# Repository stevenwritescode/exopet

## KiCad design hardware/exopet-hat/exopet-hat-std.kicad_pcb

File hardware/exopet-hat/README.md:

# ExoPet HAT — KiCad Project

Rev 1 hardware per `docs/superpowers/specs/2026-07-27-exopet-hat-design.md`.

- `exopet-hat.kicad_pro` — project
- `exopet-hat.kicad_sch` — schematic (stage 1: capture complete, layout not started)

## Status

- [x] Schematic capture (all blocks from the spec)
- [x] Review pass — done via datasheet verification (see below); GUI
      eyeball still welcome
- [x] Footprint assignment + LCSC part numbers (`exopet-hat-bom.csv`,
      see `BOM-NOTES.md` for confidence levels)
- [x] Board layout — generated placement + freerouting autoroute
      (`tools/gen_board.py`, `tools/flip_backs.py`, `tools/finish_board.py`
      pipeline); DRC fully clean (0 violations)
- [ ] Human eyeball pass on the routed board in the KiCad GUI
- [ ] JLCPCB DFM check + fab package (gerbers/BOM/CPL)
- [ ] Order prototypes

## Layout notes (rev 1)

- **Terminal grouping (per Steven):** front edge = the four relay
  channels as separated blocks, CH1 CH2 CH3 then the CH4 dry contact
  last; left edge = sensor stack: FLOAT1, FLOAT2, TEMP (3-pos screw
  terminal — 3V3/DATA/GND, no plugs or soldering).
- **Float switch inputs added** (they were missing!): FLOAT1 → GPIO16
  (tank, matches existing hub code), FLOAT2 → GPIO12 (sump spec). Each
  has 10k pull-up, 1k series protection, 100nF filter on board.
- All terminals are Phoenix PT-1,5 3.5 mm pitch (17.5 A rated — loads
  are ≤1 A).
- All SMD is on the **back side**, nested in pin-free channels between
  the through-hole fields; top side is through-hole only.
- **J5 (JST temp connector) and the TRS jack were cut** — temperature is
  the 3-pos screw terminal.
- **J2 (aux 12V input) was cut** — barrel jack is the sole input.
- Signal tracks are 0.25 mm (autorouted); bulk current rides the
  full-board GND pours and short paths. Rev 2: netclass-driven widths.
- GND zones both sides, thermal-relief pads, min spoke count relaxed to
  1 (relieved pads also carry routed GND tracks).

## Datasheet verification (done in lieu of skipped human review)

- **EZO-pH socket (J7/J12)** — verified against Atlas EZO-pH datasheet
  v6.1: top row GND, TX/SDA, RX/SCL; bottom row VCC, PRB, PGND.
- **G5LE-1 relay** — verified against Omron K100-E1-08 datasheet: coil on
  terminals 2/5, COM 1, NO 3, NC 4; KiCad footprint pad geometry matches
  the datasheet mounting-hole pattern.
- **Pololu D24V50F5** — confirmed 5 pins (EN, VIN, 2×GND, VOUT); socket is
  now 1×5. **Physical pin order must be confirmed against the module
  silkscreen at layout time.**

## pH: deferred to rev 2

Rev 1 has **no pH input** (decision 2026-07-27). The Atlas datasheet
requires electrical isolation near pumps/valves for commercial use, so
rev 2 will add the EZO socket + BNC behind an ADM3260 isolation stage
(reference circuit: EZO-pH datasheet p.8). GPIO2/3 (header pins 3/5)
are left unconnected and reserved for it.

## Conventions

- Connectivity uses global labels (`+12V`, `GPIO17`, `1WIRE_DATA`, …)
  rather than long wires — check the label, not the line.
- U2 uses the ULN2003 symbol; the BOM part is **TBD62003APG**
  (pin-compatible DMOS array, 3.3 V-safe inputs).
- PSU1 is the socketed Pololu D24V50F5 5 V/5 A buck module (rev 2:
  integrate a TPS54531 circuit).
- **Verify before layout:** PSU1 socket pin order against the
  D24V50F5 module silkscreen (EN, VIN, 2×GND, VOUT).

## Opening

KiCad 8+. `File → Open Project → exopet-hat.kicad_pro`.
Run ERC: Inspect → Electrical Rules Checker.

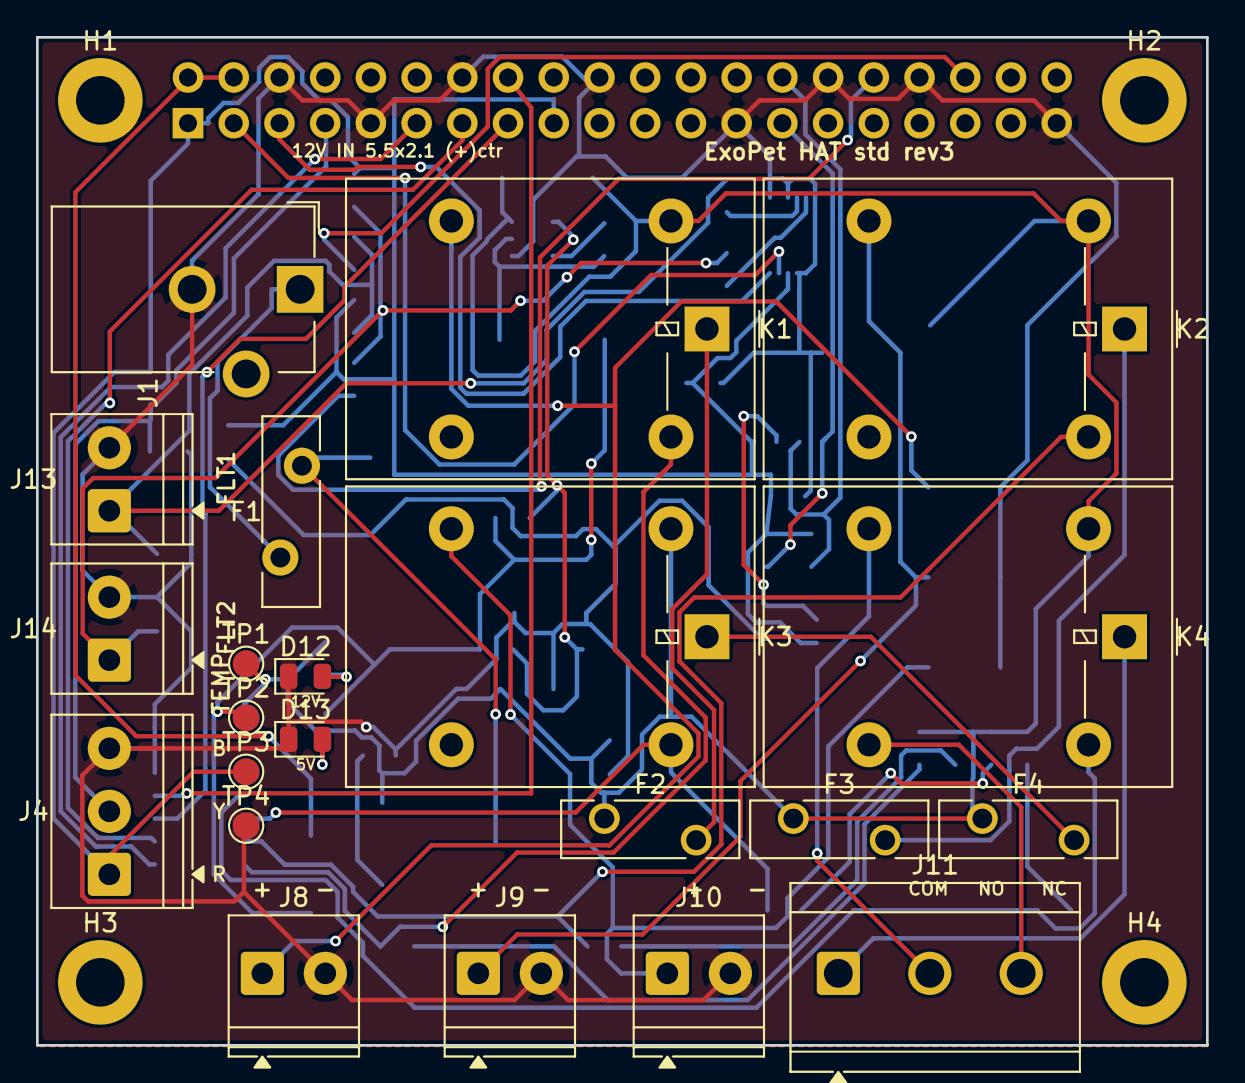
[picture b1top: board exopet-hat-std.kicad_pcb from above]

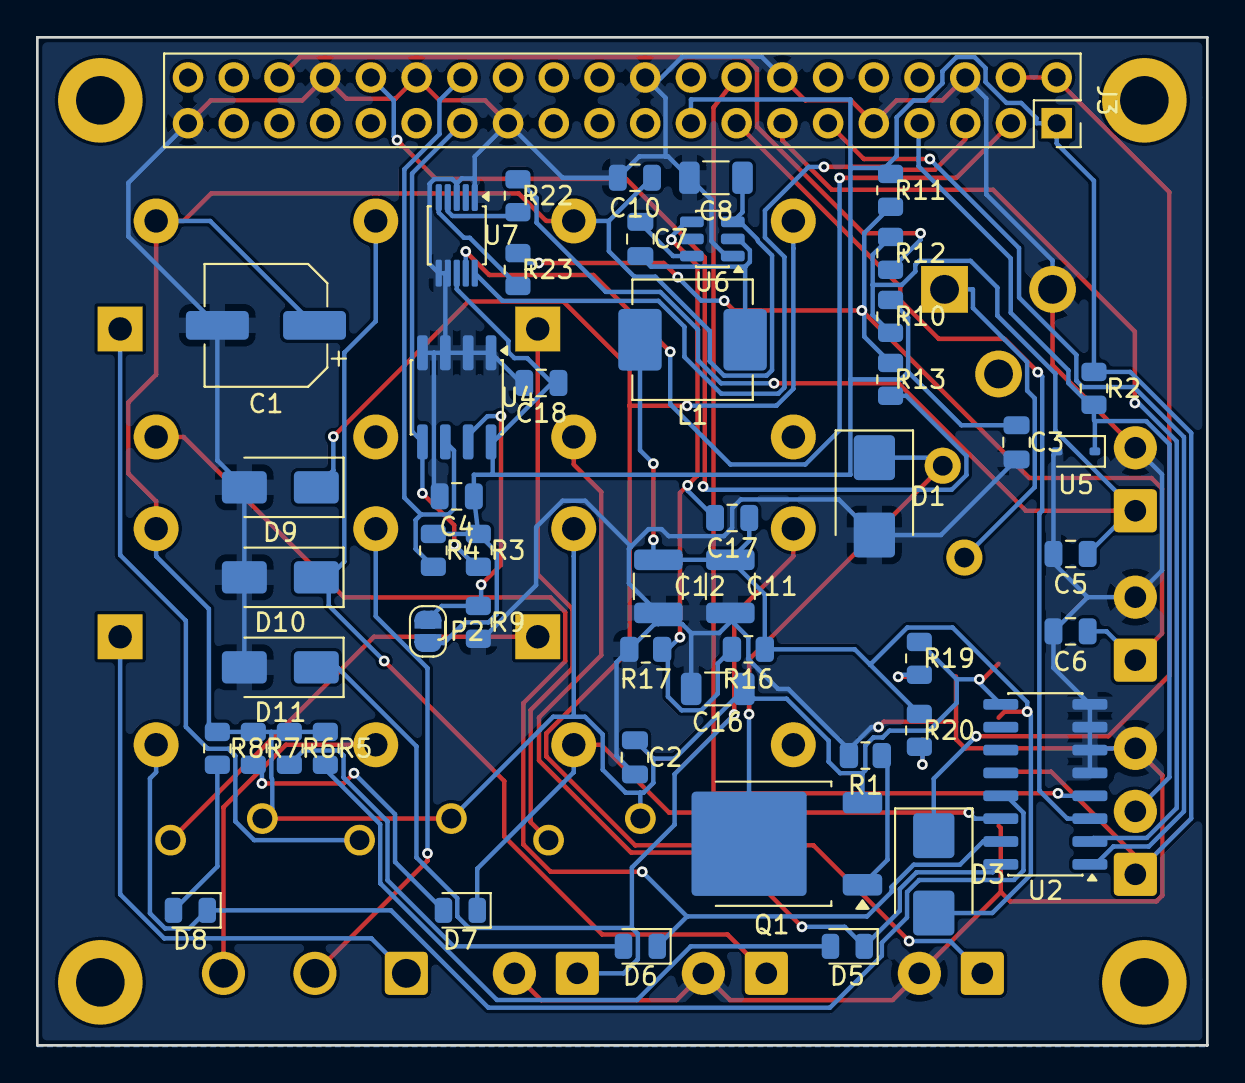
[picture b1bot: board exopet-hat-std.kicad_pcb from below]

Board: 2 copper layers, 65.0 x 56.0 mm, 77 parts (51 on the bottom side), 46 nets.

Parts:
C1: CP_Elec_6.3x7.7
C2, C3, C4, C5, C6, C7, C10, C17, C18: C_0805_2012Metric
C8, C16: C_1206_3216Metric
C11, C12: C_1210_3225Metric
D1, D3: D_SMB
D5, D6, D7, D8, D12, D13: LED_0805_2012Metric
D9, D10, D11: D_SMA
F1: Fuse_Bourns_MF-RG500
F2, F3, F4: Fuse_Bourns_MF-RHT100
H1, H2, H3, H4: MountingHole_2.7mm_M2.5_DIN965_Pad
J1: BarrelJack_CUI_PJ-102AH_Horizontal
J3: PinSocket_2x20_P2.54mm_Vertical
J4: TerminalBlock_Phoenix_PT-1,5-3-3.5-H_1x03_P3.50mm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; TerminalBlock_Phoenix_PT-1,5-3-3.5-H_1x03_P3.50mm_Horizontal
J8, J9, J10, J13, J14: TerminalBlock_Phoenix_PT-1,5-2-3.5-H_1x02_P3.50mm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; TerminalBlock_Phoenix_PT-1,5-2-3.5-H_1x02_P3.50mm_Horizontal
J11: TerminalBlock_CUI_TB007-508-03_1x03_P5.08mm_Horiz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; TerminalBlock_CUI_TB007-508-03_1x03_P5.08mm_Horizontal
JP2: SolderJumper-2_P1.3mm_Open_RoundedPad1.0x1.5mm
K1, K2, K3, K4: Relay_SPDT_Omron-G5LE-1
L1: L_Vishay_IHLP-2525
Q1: TO-252-2
R1, R2, R3, R4, R5, R6, R7, R8, R9, R10, R11, R12, R13, R16, R17, R19, R20, R22, R23: R_0805_2012Metric
TP1, TP2, TP3, TP4: TestPoint_Pad_D1.5mm
U2: SOIC-16_3.9x9.9mm_P1.27mm
U4: SOIC-8_3.9x4.9mm_P1.27mm
U5: D_SOD-323
U6: SOT-23-6
U7: MSOP-10_3x3mm_P0.5mm

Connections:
1WIRE_DATA: J3.7, J4.2, R2.2, U5.1
+3V3: C3.1, C4.1, C18.1, J3.1, J3.17, J4.1, JP2.2, R2.1, R3.1, R4.1, R10.1, R11.1, TP3.1, U4.8, U7.8
+5V: D3.1, J3.2, J3.4
+5V_BUCK: C11.1, C12.1, C17.1, D3.2, L1.2, R16.1, R20.1, TP2.1
+12V: C1.1, C2.1, C8.1, C10.1, C16.1, F2.1, F3.1, F4.1, K1.2, K2.2, K3.2, K4.2, Q1.3, R5.1, R6.1, R7.1, R8.1, R19.1, TP1.1, U2.9, U6.3
+12V_F: D1.1, F1.2, Q1.2
+12V_IN: F1.1, J1.1
BUCK_BOOT: C7.1, U6.6
BUCK_FB: C17.2, R16.2, R17.1, U6.4
BUCK_SW: C7.2, L1.1, U6.2
CH1_FUSED: F2.2, K1.1
CH1_OUT: D9.1, J8.1, K1.3
CH2_FUSED: F3.2, K2.1
CH2_OUT: D10.1, J9.1, K2.3
CH3_FUSED: F4.2, K3.1
CH3_OUT: D11.1, J10.1, K3.3
CH4_COM: J11.1, K4.1
CH4_NC: J11.3, K4.4
CH4_NO: J11.2, K4.3
EEPROM_SCL: J3.28, R4.2, U4.6
EEPROM_SDA: J3.27, R3.2, U4.5
EEPROM_WP: JP2.1, R9.1, U4.7
FLOAT1_GPIO: J3.36, R12.2
FLOAT1_SW: C5.1, J13.1, R10.2, R12.1, R22.1
FLOAT2_GPIO: J3.32, R13.2
FLOAT2_SW: C6.1, J14.1, R11.2, R13.1, R23.1
FLT1_SENSE: R22.2, U7.4
FLT2_SENSE: R23.2, U7.5
GND: C1.2, C2.2, C3.2, C4.2, C5.2, C6.2, C8.2, C10.2, C11.2, C12.2, C16.2, C18.2, D1.2, D9.2, D10.2, D11.2, D12.1, D13.1, J1.2, J3.6, J3.9, J3.14, J3.20, J3.25, J3.30, J3.34, J3.39, J4.3, J8.2, J9.2, J10.2, J13.2, J14.2, R1.2, R9.2, R17.2, TP4.1, U2.5, U2.6, U2.7, U2.8, U4.1, U4.2, U4.3, U4.4, U5.2, U6.1, U7.1, U7.3, U7.6, U7.7
GPIO17: J3.11, U2.1
GPIO22: J3.15, U2.3
GPIO23: J3.16, U2.4
GPIO27: J3.13, U2.2
I2C1_SCL: J3.5, U7.10
I2C1_SDA: J3.3, U7.9
LED1_A: D5.2, R5.2
LED2_A: D6.2, R6.2
LED3_A: D7.2, R7.2
LED4_A: D8.2, R8.2
LED5V_A: D13.2, R20.2
LED12V_A: D12.2, R19.2
Q1_G: Q1.1, R1.1
RLY1_DRV: D5.1, K1.5, U2.16
RLY2_DRV: D6.1, K2.5, U2.15
RLY3_DRV: D7.1, K3.5, U2.14
RLY4_DRV: D8.1, K4.5, U2.13

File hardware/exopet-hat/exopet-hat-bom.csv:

"Reference","Value","Footprint","LCSC"
"C1","330uF 25V low-profile <=7.7mm","Capacitor_SMD:CP_Elec_6.3x7.7","VERIFY"
"C2-C6","100nF","Capacitor_SMD:C_0805_2012Metric","C49678"
"D1","SMBJ16A","Diode_SMD:D_SMB","VERIFY"
"D5-D8","green","LED_SMD:LED_0805_2012Metric","C2297"
"D9-D11","SS34","Diode_SMD:D_SMA","C8678"
"F1","MF-RG500 5A","Fuse:Fuse_Bourns_MF-RG500","VERIFY"
"F2-F4","MF-RHT100 1A","Fuse:Fuse_Bourns_MF-RHT100","VERIFY"
"J1","12V DC in","Connector_BarrelJack:BarrelJack_CUI_PJ-102AH_Horizontal",""
"J3","RPi GPIO (HAT)","Connector_PinSocket_2.54mm:PinSocket_2x20_P2.54mm_Vertical",""
"J4","TEMP (3V3/DATA/GND)","TerminalBlock_Phoenix:TerminalBlock_Phoenix_PT-1,5-3-3.5-H_1x03_P3.50mm_Horizontal",""
"J8","CH1 12V OUT","TerminalBlock_Phoenix:TerminalBlock_Phoenix_PT-1,5-2-3.5-H_1x02_P3.50mm_Horizontal",""
"J9","CH2 12V OUT","TerminalBlock_Phoenix:TerminalBlock_Phoenix_PT-1,5-2-3.5-H_1x02_P3.50mm_Horizontal",""
"J10","CH3 12V OUT","TerminalBlock_Phoenix:TerminalBlock_Phoenix_PT-1,5-2-3.5-H_1x02_P3.50mm_Horizontal",""
"J11","CH4 dry contact","TerminalBlock_Phoenix:TerminalBlock_Phoenix_PT-1,5-3-3.5-H_1x03_P3.50mm_Horizontal",""
"J13","FLOAT1 switch","TerminalBlock_Phoenix:TerminalBlock_Phoenix_PT-1,5-2-3.5-H_1x02_P3.50mm_Horizontal",""
"J14","FLOAT2 switch","TerminalBlock_Phoenix:TerminalBlock_Phoenix_PT-1,5-2-3.5-H_1x02_P3.50mm_Horizontal",""
"JP1","5V link (open = USB-C debug)","Jumper:SolderJumper-2_P1.3mm_Open_RoundedPad1.0x1.5mm",""
"JP2","WP (close = protect)","Jumper:SolderJumper-2_P1.3mm_Open_RoundedPad1.0x1.5mm",""
"K1-K4","G5LE-1-CF DC12","Relay_THT:Relay_SPDT_Omron-G5LE-1","C1524650"
"PSU1","Pololu D24V50F5 5V/5A","Connector_PinSocket_2.54mm:PinSocket_1x05_P2.54mm_Vertical",""
"Q1","AOD403","Package_TO_SOT_SMD:TO-252-2","C28969"
"R1","100k","Resistor_SMD:R_0805_2012Metric","C17407"
"R2","4.7k","Resistor_SMD:R_0805_2012Metric","C17673"
"R3,R4","3.9k","Resistor_SMD:R_0805_2012Metric","C26010"
"R5-R8","2.2k","Resistor_SMD:R_0805_2012Metric","C17520"
"R9-R11","10k","Resistor_SMD:R_0805_2012Metric","C17414"
"R12,R13","1k","Resistor_SMD:R_0805_2012Metric","C17513"
"U2","TBD62003AFG","Package_SO:SOIC-16_3.9x9.9mm_P1.27mm","C163227"
"U4","CAT24C32","Package_SO:SOIC-8_3.9x4.9mm_P1.27mm","VERIFY"
"U5","5V ESD clamp (SOD-323)","Diode_SMD:D_SOD-323","C19224"

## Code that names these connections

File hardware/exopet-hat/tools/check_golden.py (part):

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    "C17": {"1": "+5V_BUCK", "2": "BUCK_FB"},
    # relay driver: GPIO 17/27/22/23 in, open-drain sinks out,
    # COM (flyback) pin on +12V
    "U2": {"1": "GPIO17", "2": "GPIO27", "3": "GPIO22", "4": "GPIO23",
           "5": "GND", "6": "GND", "7": "GND", "8": "GND", "9": "+12V",
           "16": "RLY1_DRV", "15": "RLY2_DRV", "14": "RLY3_DRV",
           "13": "RLY4_DRV", "10": NC, "11": NC, "12": NC},
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    "J14": {"1": "FLOAT2_SW", "2": "GND"},
    "R10": {"1": "+3V3", "2": "FLOAT1_SW"},
    "R11": {"1": "+3V3", "2": "FLOAT2_SW"},
    "R12": {"1": "FLOAT1_SW", "2": "FLOAT1_GPIO"},
    "R13": {"1": "FLOAT2_SW", "2": "FLOAT2_GPIO"},
    "C5": {"1": "FLOAT1_SW", "2": "GND"},
    "C6": {"1": "FLOAT2_SW", "2": "GND"},
    # HAT ID EEPROM
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           "6": "GND", "9": "GND", "14": "GND", "20": "GND",
           "25": "GND", "30": "GND", "34": "GND", "39": "GND",
           "7": "1WIRE_DATA",
           "11": "GPIO17", "13": "GPIO27", "15": "GPIO22",
           "16": "GPIO23",
           "27": "EEPROM_SDA", "28": "EEPROM_SCL",
           "36": "FLOAT1_GPIO", "32": "FLOAT2_GPIO",
           "3": "I2C1_SDA", "5": "I2C1_SCL", "8": NC, "10": NC, "12": NC, "18": NC,
           "19": NC, "21": NC, "22": NC, "23": NC, "24": NC, "26": NC,
           "29": NC, "31": NC, "33": NC, "35": NC, "37": NC, "38": NC,
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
